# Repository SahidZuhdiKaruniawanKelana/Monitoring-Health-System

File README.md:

# Cliniscan
<p align="center" style="font-size:38px"><strong>Sistem Monitoring Kesehatan Tubuh Berdasarkan Detak Jantung dan Suhu Tubuh</strong></p>

CliniScan adalah alat pemantau kesehatan berbasis mikrokontroler yang dirancang untuk memonitor detak jantung dan suhu tubuh secara real-time.  Dengan memanfaatkan sensor Max30100 dan DS18b20, CliniScan memberikan data vital secara akurat dan langsung ditampilkan pada layar monitoring .  Alat ini dirancang untuk mendukung pemantauan kondisi tubuh secara praktis dan efisien, terutama dalam lingkungan sehari-hari.

# 🛠️ How It Works

- **Pengukuran Data Secara Real-Time**: CliniScan menggunakan sensor untuk memantau detak jantung dan suhu tubuh secara langsung dan terus-menerus.
- **Pemrosesan Data**: Data yang dikumpulkan dari sensor akan diolah oleh mikrokontroler untuk menentukan kondisi kesehatan pengguna.
- **Klasifikasi Status Kesehatan**: Sistem mengklasifikasikan status pengguna berdasarkan ambang batas tertentu:
  - **Aman**: Detak jantung dan suhu tubuh berada dalam rentang normal.
  - **Bahaya**: Terdapat penyimpangan yang dapat mengindikasikan masalah kesehatan.
- **Tampilan Hasil**: Status kesehatan akan ditampilkan secara langsung melalui layar monitoring, sehingga pengguna dapat segera mengetahui kondisi tubuh mereka.

# 🚀 Features
- **Pemantauan kesehatan real-time**: CliniScan secara terus-menerus mengukur suhu tubuh dan detak jantung pengguna.
- **Penyimpanan lokal mikrokontroler**: Data sensor diproses dan ditampilkan langsung tanpa bergantung pada koneksi internet.
- **Antarmuka LCD sederhana**: Informasi ditampilkan secara langsung melalui layar LCD, memberikan pengalaman pengguna yang praktis dan informatif.

# Lecturer Profile

<p  align="center"><b>
Akhmad Hendriawan ST. MT.<br>
NIP. 197501272002121003</b>
</p>

# 💰 The Stakeholders :

| **No** | **Name**                          | **Role**                      |
|--------|-----------------------------------|-------------------------------|
| 1      | Farhan Bayu Pamungkas             | Hardware Developer            |
| 2      | Dariel Afron Zah Maulana          | Back End Software Developer   |
| 3      | Akmal Aditya                      | Front End Software Developer  |
| 4      | Fiqinnajach Almakhi               | Product Designer              |
| 5      | Muhammad Ammar Tsaqif             | PCB Designer                  |
| 6      | Sahid Zuhdi Karuniawan Kelana     | Product Finalization          |

# 💻 Hardware
**Schematic Design**

**PCB Design shield**

**3D Design**

# 🌐 Software
**Flowchart**

**Blok Diagram**

PCB Jadi

</p>

# 💼 Product Prototype
**Product Illustration**

**Final Product**

# 🌐 Software Prototype
Link Youtube: https://youtu.be/AOL8eu1ZVWA

# 🌐 Realisasi Program
https://github.com/user-attachments/assets/89dac77f-7542-4013-814b-a6df4c413755

Link Youtube: https://youtu.be/bUS6ud4mv1k

# 🌐 Cara Kerja
https://github.com/user-attachments/assets/06356922-0a25-4428-9938-26c5c88da9af

Link Youtube: https://youtube.com/shorts/00xpaAIdKis?feature=share

# 💵 Rincian Biaya

|**Item**|**Jumlah**|**Harga Satuan (Rp)**|**Total (Rp)**|
|:--:|:--:|:--:|:--:|
|Arduino UNO|1|100.000|100.000|
|Max 30102|1|25.000|25.000|
|DS18B20|1|6.000|6.000|
|Resistor 4.7K|10|100|1000|
|LCD I2C|1|20.000|20.000|
|Buzzer|1|10.000|10.000|
|Cetak PCB|1|10.000|10.000|
|Cetak 3D|1|12.500|12.500|
|Total Biaya|---|---|**184.500**|

# 🌐 Link Presentasi Canva
https://www.canva.com/design/DAGlpKlKbUI/rwsxZAOyYzx1ZmiQSskNvg/edit?utm_content=DAGlpKlKbUI&utm_campaign=designshare&utm_medium=link2&utm_source=sharebutton

# 🌐 Video Preview
https://github.com/user-attachments/assets/ae47b2bd-4c72-4982-bb75-b28a39751431

Link Youtube: https://youtu.be/Ds7KlVZ7kMw

# 🌐 Simulasi wokwi
https://github.com/user-attachments/assets/c8ba4219-e30b-4996-9bfd-4bf6193c81ce

Link Simulasi:https://wokwi.com/projects/430136088909636609

# Flyer

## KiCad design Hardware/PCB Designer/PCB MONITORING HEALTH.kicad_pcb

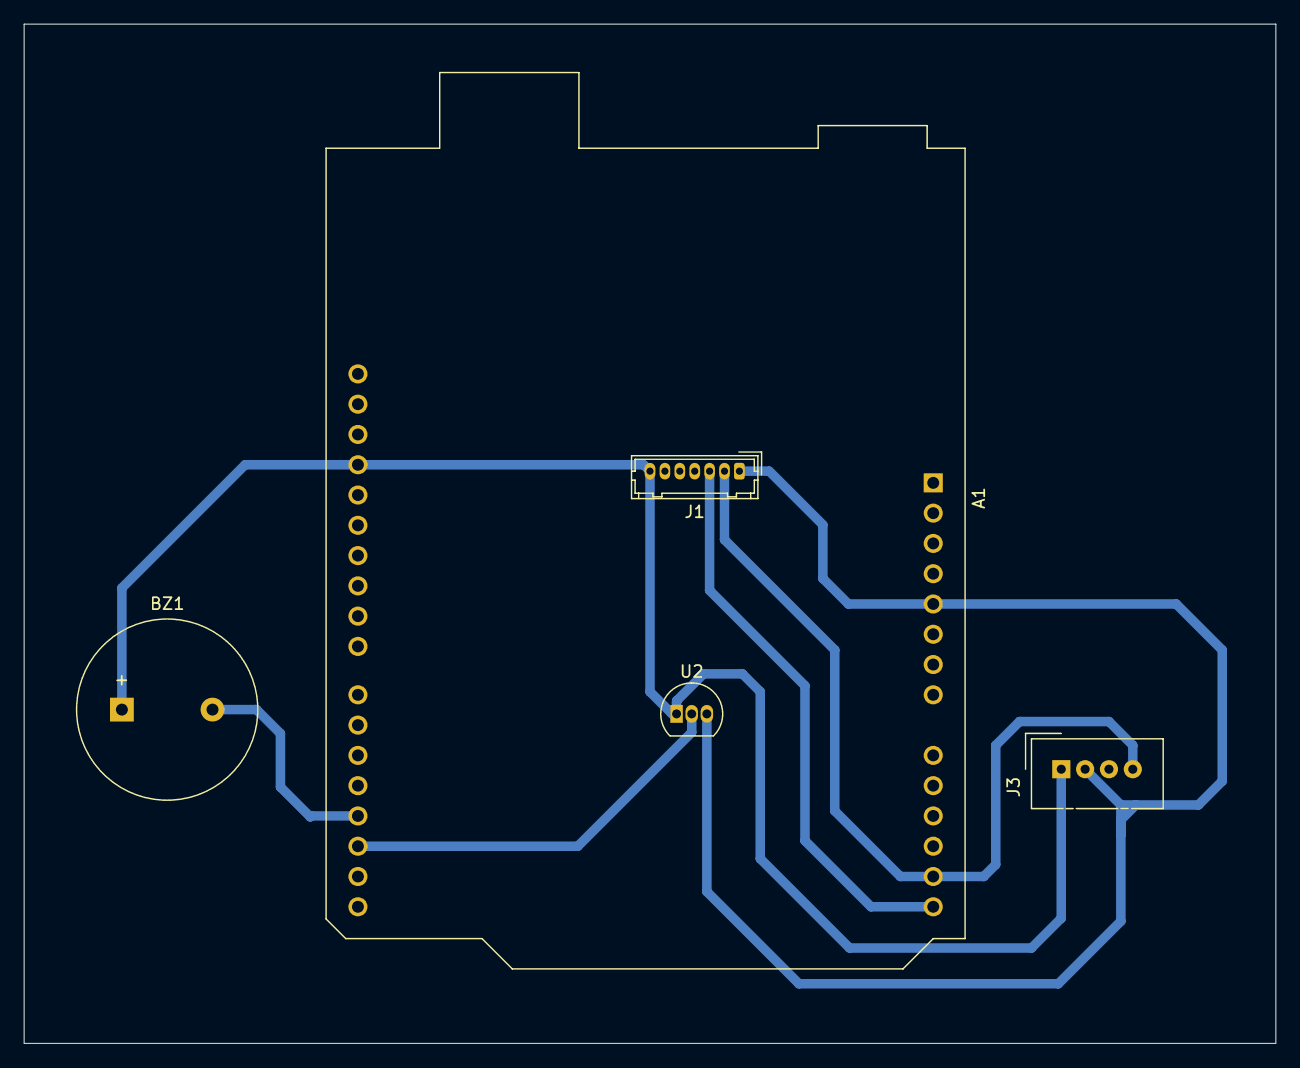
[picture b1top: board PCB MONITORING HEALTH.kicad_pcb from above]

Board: 2 copper layers, 105.0 x 85.5 mm, 5 parts (0 on the bottom side), 5 nets.

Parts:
A1: Arduino_UNO_R3
BZ1: Buzzer; Buzzer_15x7.5RM7.6
J1: MAX30102; Hirose_DF13-07P-1.25DSA_1x07_P1.25mm_Vertical
J3: LCD 16x2; NS-Tech_Grove_1x04_P2mm_Vertical
U2: DS18B20; TO-92_Inline

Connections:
/GND: A1.29 (GND), BZ1.1 (+), J1.7, J3.1, U2.1 (GND)
/SCL: A1.13 (SDA/A4), A1.14 (SCL/A5), J1.2, J1.3, J3.3, J3.4
/VCC: A1.5 (+5V), J1.1, J3.2, U2.3 (V_{DD})
unnamed: A1.17 (D2), U2.2 (DQ)
unnamed: A1.18 (D3), BZ1.2 (-)

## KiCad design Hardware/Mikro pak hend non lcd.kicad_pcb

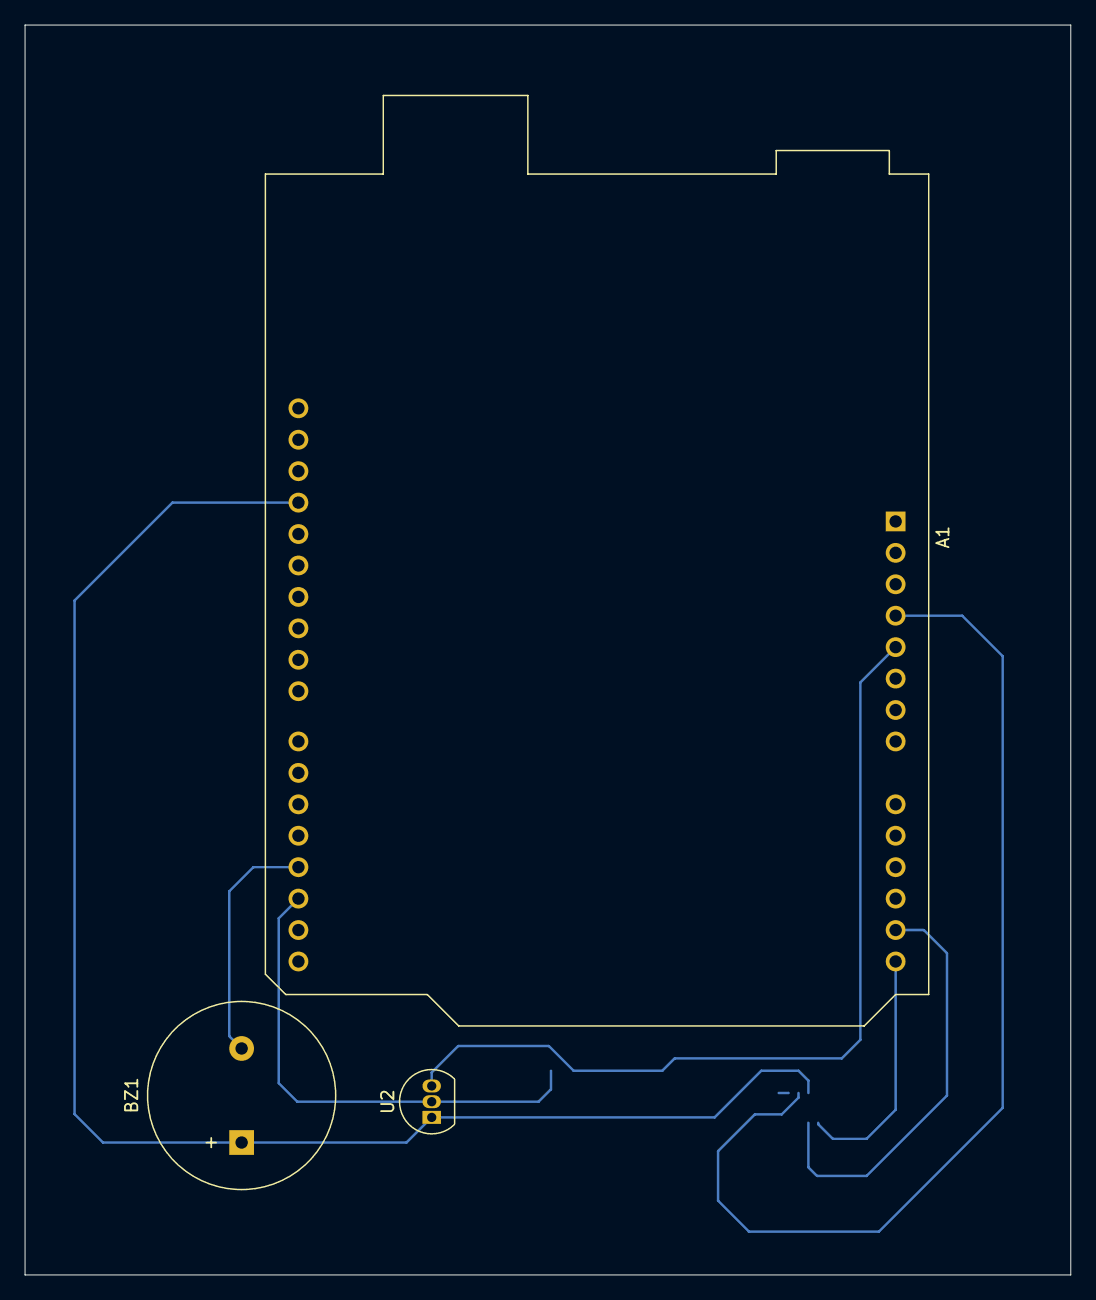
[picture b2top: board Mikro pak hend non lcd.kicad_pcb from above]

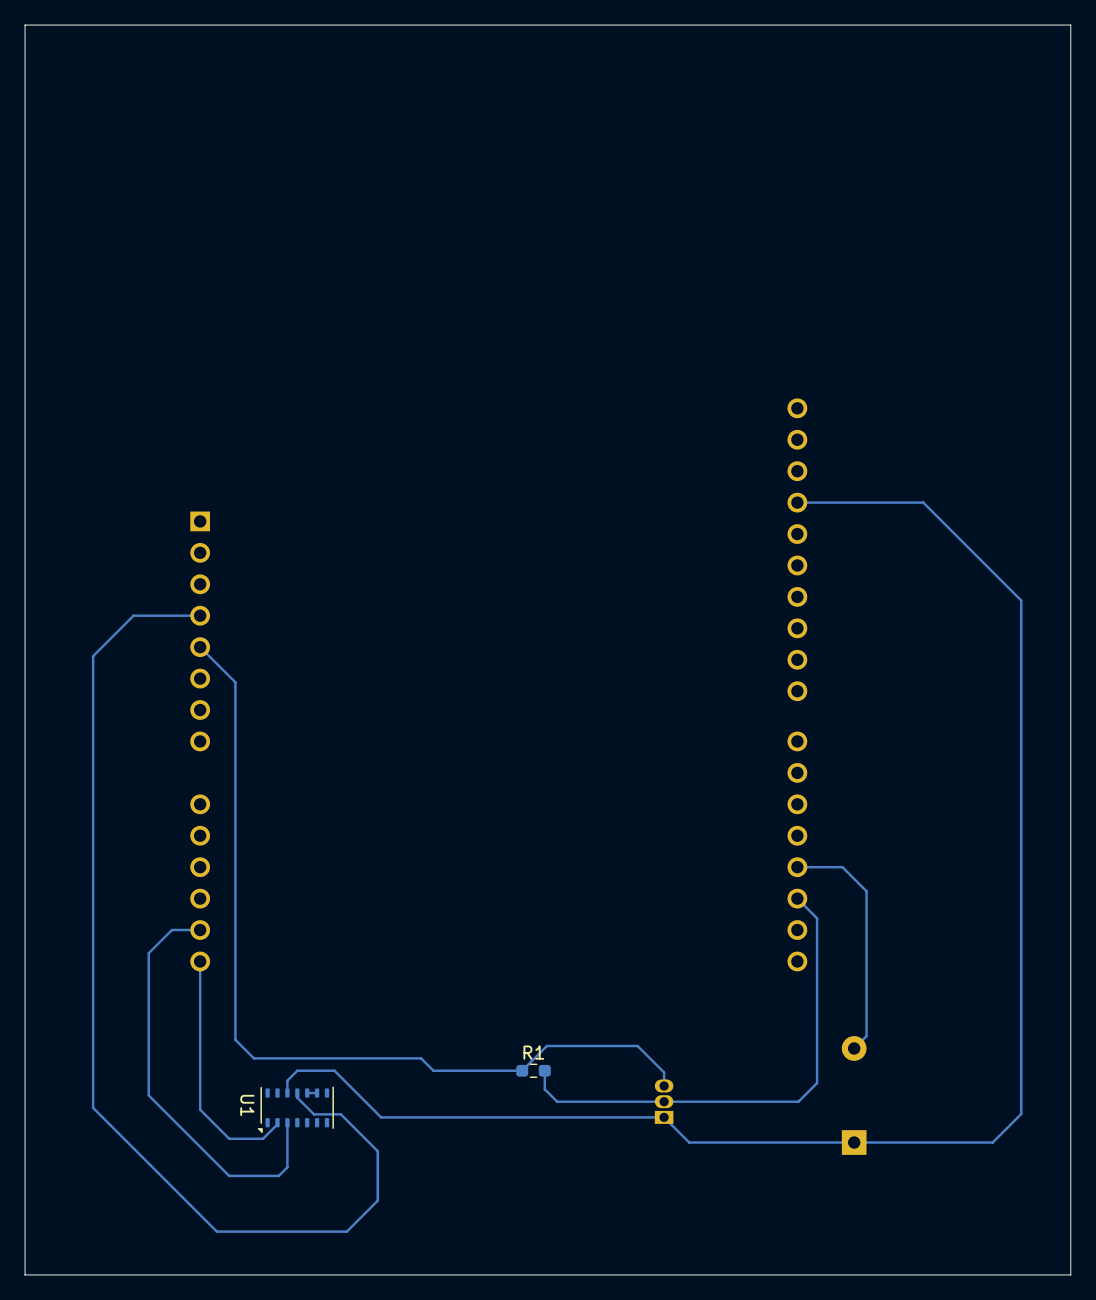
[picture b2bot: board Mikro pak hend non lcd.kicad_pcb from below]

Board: 2 copper layers, 84.5 x 101.0 mm, 5 parts (2 on the bottom side), 8 nets.

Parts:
A1: Arduino_UNO_R3
BZ1: Buzzer; Buzzer_15x7.5RM7.6
R1: 4.7K; R_0603_1608Metric_Pad0.98x0.95mm_HandSolder
U1: MAX30102; Maxim_OLGA-14_3.3x5.6mm_P0.8mm
U2: DS18B20; TO-92_Inline

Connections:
unnamed: A1.4 (3V3), U1.11 (VDD)
unnamed: A1.5 (+5V), R1.1, U2.3 (V_{DD})
unnamed: A1.17 (D2), R1.2, U2.2 (DQ)
unnamed: A1.18 (D3), BZ1.2 (-)
unnamed: A1.29 (GND), BZ1.1 (+), U1.12 (GND), U2.1 (GND)
unnamed: A1.14 (SCL/A5), U1.2 (SCL)
unnamed: A1.13 (SDA/A4), U1.3 (SDA)
unnamed: U1.9 (VLED+), U1.10 (VLED+)

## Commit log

2025-04-21 Create Assets
2025-04-21 Update Assets
2025-04-21 Create Temp
2025-04-21 Create L
2025-04-21 Create Dokumentasi
2025-04-21 Create Hardware
2025-04-21 Create Program
2025-04-21 Create Desain 3D
2025-04-21 Program Simulasi
2025-04-24 Create Codingan final
2025-04-28 Add files via upload
    file pototye figma ui ux designer
2025-04-28 Rename image.png to UI UX design .png
2025-04-29 Rename ChatGPT Image Apr 28, 2025, 10_26_54 PM.png to FlowChart Prototype.png
2025-05-06 Create 1
2025-05-07 Create png
2025-05-07 Create p
2025-05-07 Create jadi
2025-05-07 Create Desain 2
2025-05-07 Create 2
2025-05-07 Create Foto
2025-05-08 Rename Screenshot 2025-05-08 230047.png to Desain Readme
2025-05-17 Code Rangkaian
2025-05-25 Rename 1 to Program 1 ( BPM dan Suhu +AVG)
2025-05-25 Rename 2 to Program Simpel GUI
2025-06-02 Create program 2 pengambilan sample lebih cepat
2025-06-02 Create program final
2025-06-03 Ranfkaian Final
2025-06-03 Update TAMPILAN HITAM
2025-06-03 Create TAMPILAN PUTIH
2025-06-03 Rename Simulasi 1.png to Skematik Shield 1.png
2025-06-03 Rename Simulasi 2.png to Skematik Shield 2.png
2025-06-03 Rename 3D PCB MONITORING.png to 3D PCB shield github.png
2025-06-03 Rename Wiring Rangkaian.jpg to PCB jadi.jpg
